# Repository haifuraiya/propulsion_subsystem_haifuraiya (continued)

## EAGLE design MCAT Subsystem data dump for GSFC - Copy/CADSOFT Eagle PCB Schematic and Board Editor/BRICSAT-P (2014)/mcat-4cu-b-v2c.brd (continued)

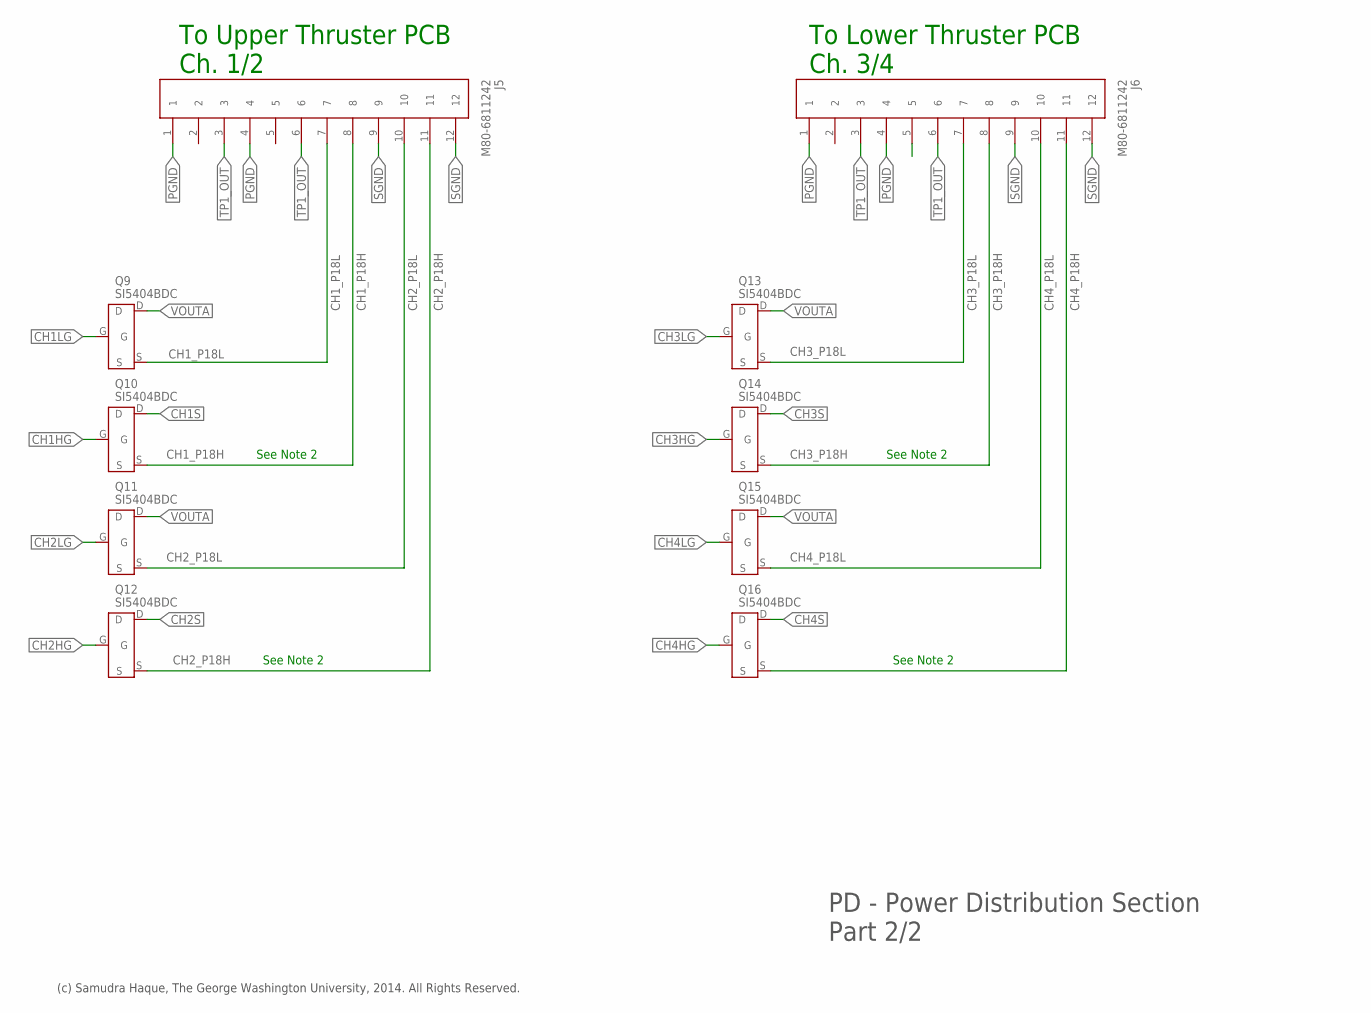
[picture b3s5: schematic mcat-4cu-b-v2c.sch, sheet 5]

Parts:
J5, J6: M80-6811242; M80-68112
Q9, Q10, Q11, Q12, Q13, Q14, Q15, Q16: SI5404BDC; 1206-8-CHIPFET

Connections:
CH1HG: Q10.G; also elsewhere on the board
CH1LG: Q9.G; also elsewhere on the board
CH1S: Q10.D; also elsewhere on the board
CH1_P18H: J5.8, Q10.S
CH1_P18L: J5.7, Q9.S
CH2HG: Q12.G; also elsewhere on the board
CH2LG: Q11.G; also elsewhere on the board
CH2S: Q12.D; also elsewhere on the board
CH2_P18H: J5.11, Q12.S
CH2_P18L: J5.10, Q11.S
CH3HG: Q14.G; also elsewhere on the board
CH3LG: Q13.G; also elsewhere on the board
CH3S: Q14.D; also elsewhere on the board
CH3_P18H: J6.8, Q14.S
CH3_P18L: J6.7, Q13.S
CH4HG: Q16.G; also elsewhere on the board
CH4LG: Q15.G; also elsewhere on the board
CH4S: Q16.D; also elsewhere on the board
CH4_P18H: J6.11, Q16.S
CH4_P18L: J6.10, Q15.S
PGND: J5.1, J5.4, J6.1, J6.4; also elsewhere on the board
SGND: J5.9, J5.12, J6.9, J6.12; also elsewhere on the board
TP1_OUT: J5.3, J5.6, J6.3, J6.6; also elsewhere on the board
VOUTA: Q9.D, Q11.D, Q13.D, Q15.D; also elsewhere on the board

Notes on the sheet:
PD - Power Distribution Section Part 2/2
(c) Samudra Haque, The George Washington University, 2014. All Rights Reserved.
See Note 2
To Upper Thruster PCB Ch. 1/2
To Lower Thruster PCB Ch. 3/4

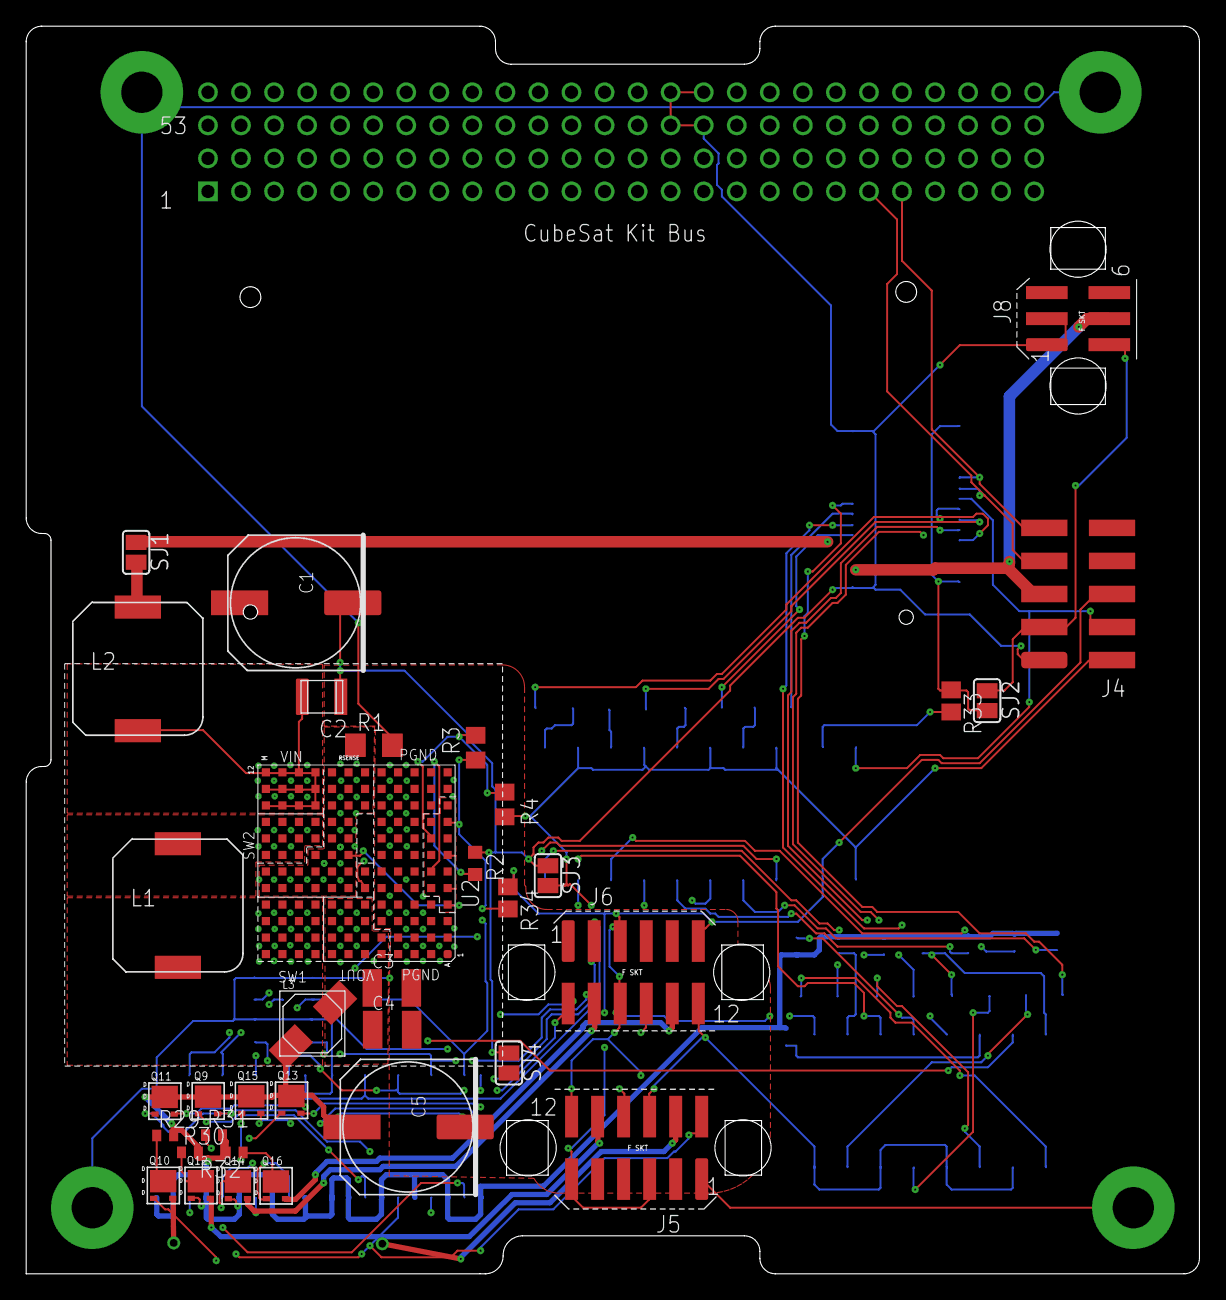
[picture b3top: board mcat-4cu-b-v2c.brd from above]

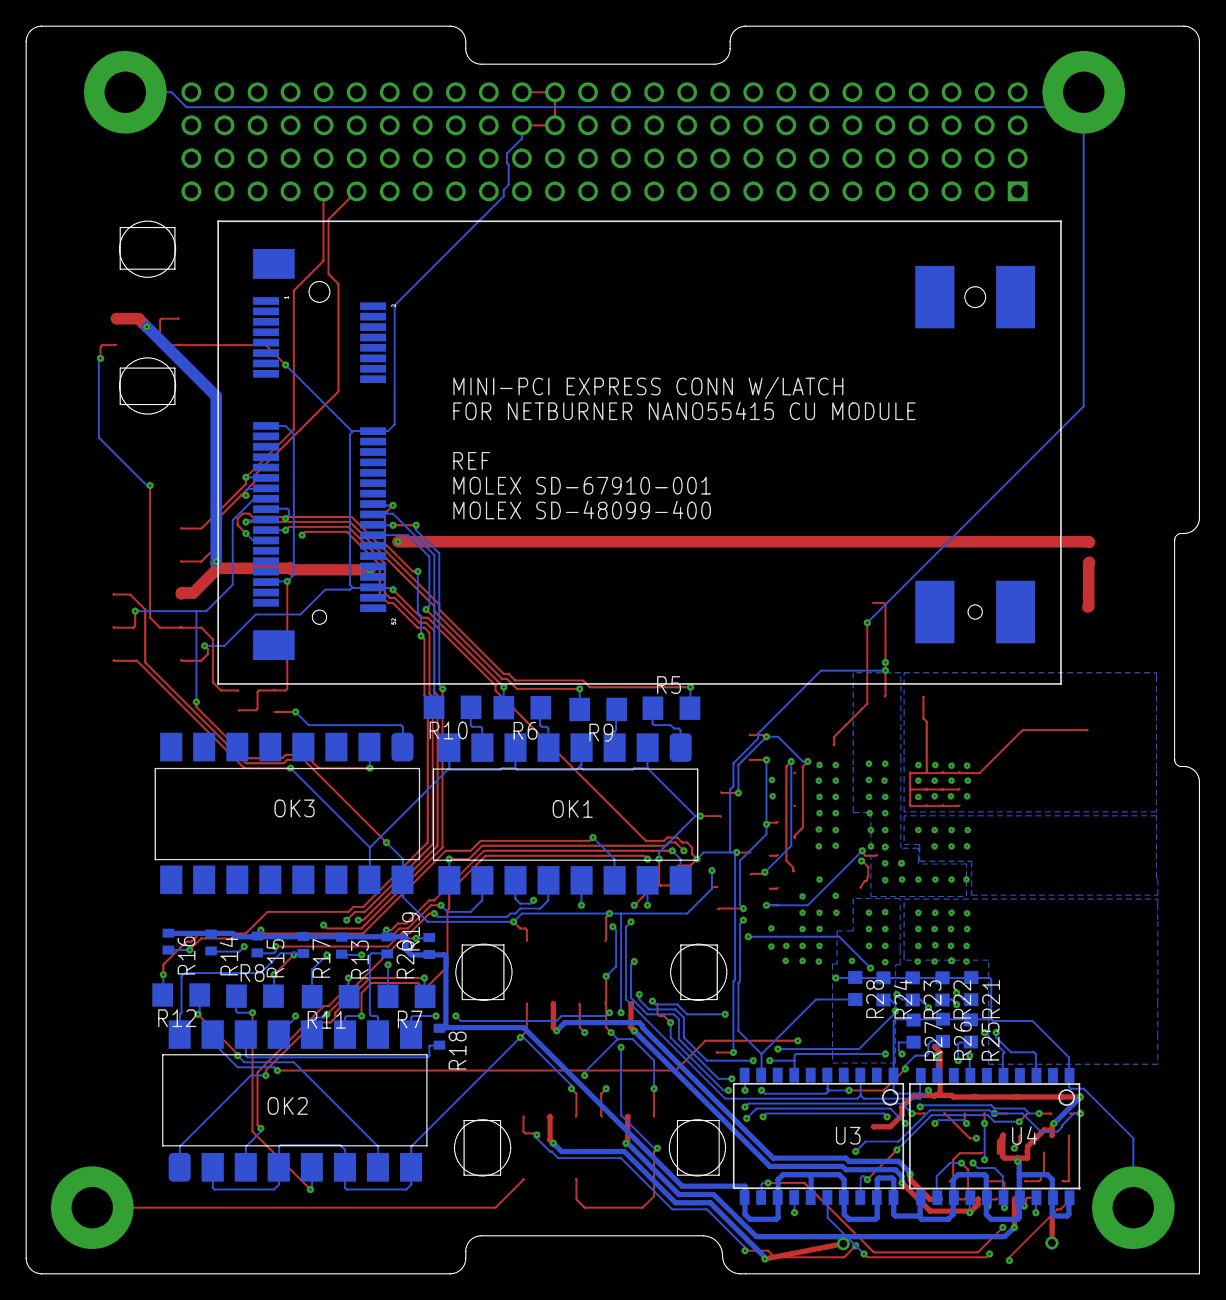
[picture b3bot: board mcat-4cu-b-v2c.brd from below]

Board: 4 copper layers, 90.2 x 95.9 mm, 70 parts (30 on the bottom side), 73 nets.

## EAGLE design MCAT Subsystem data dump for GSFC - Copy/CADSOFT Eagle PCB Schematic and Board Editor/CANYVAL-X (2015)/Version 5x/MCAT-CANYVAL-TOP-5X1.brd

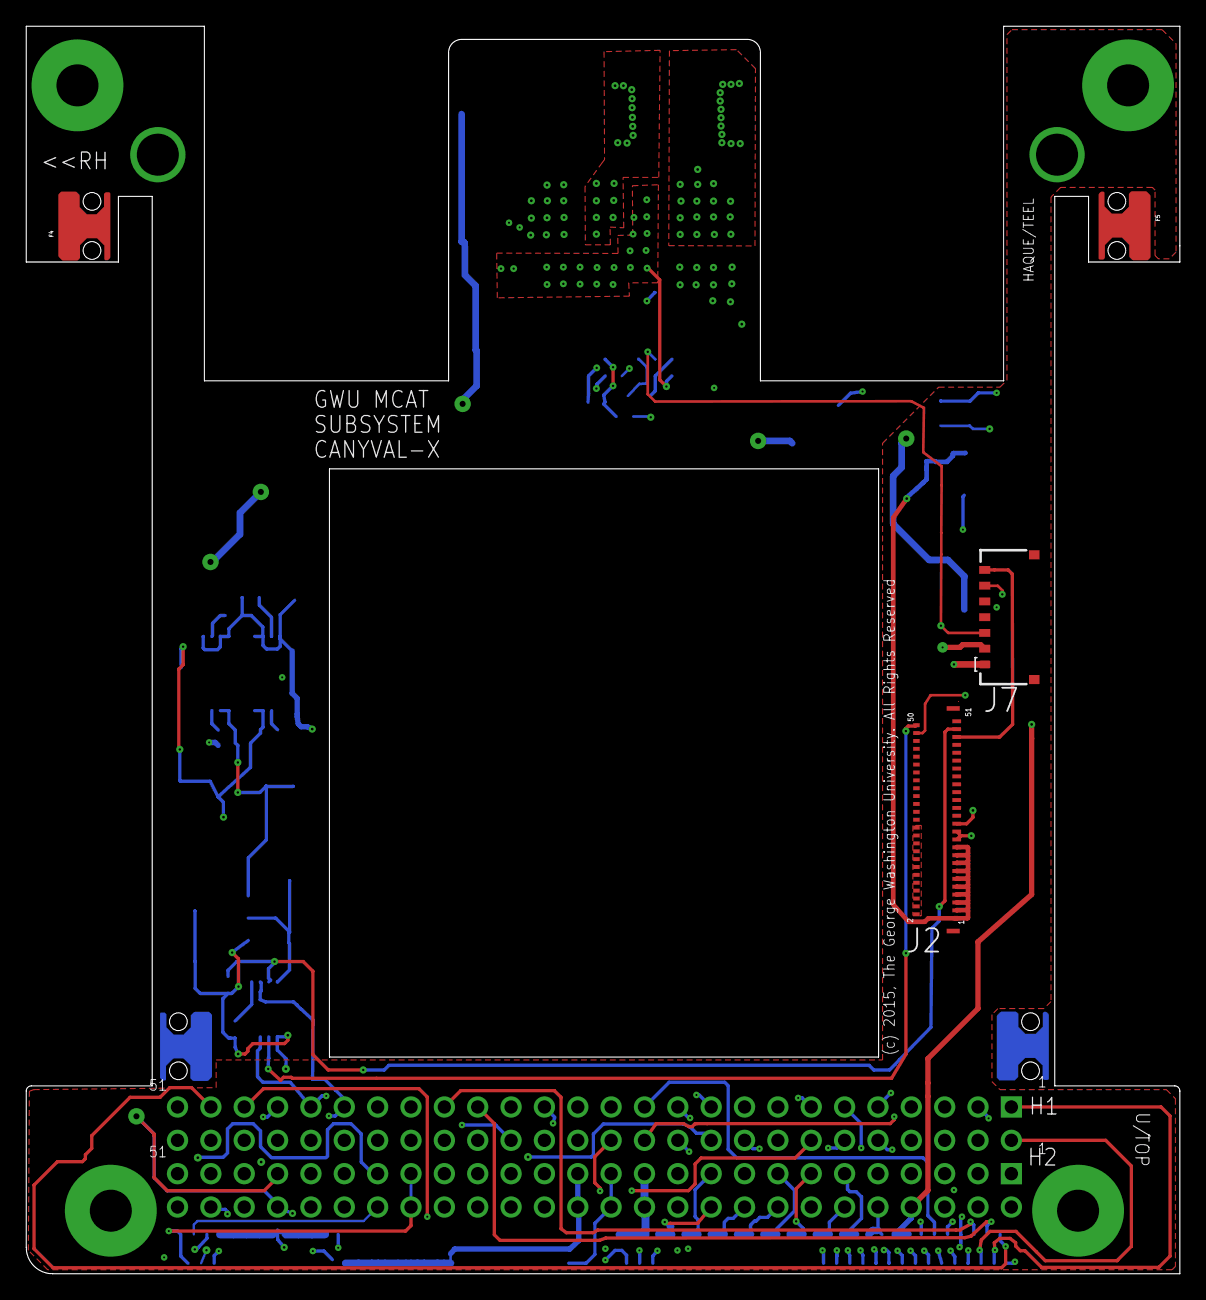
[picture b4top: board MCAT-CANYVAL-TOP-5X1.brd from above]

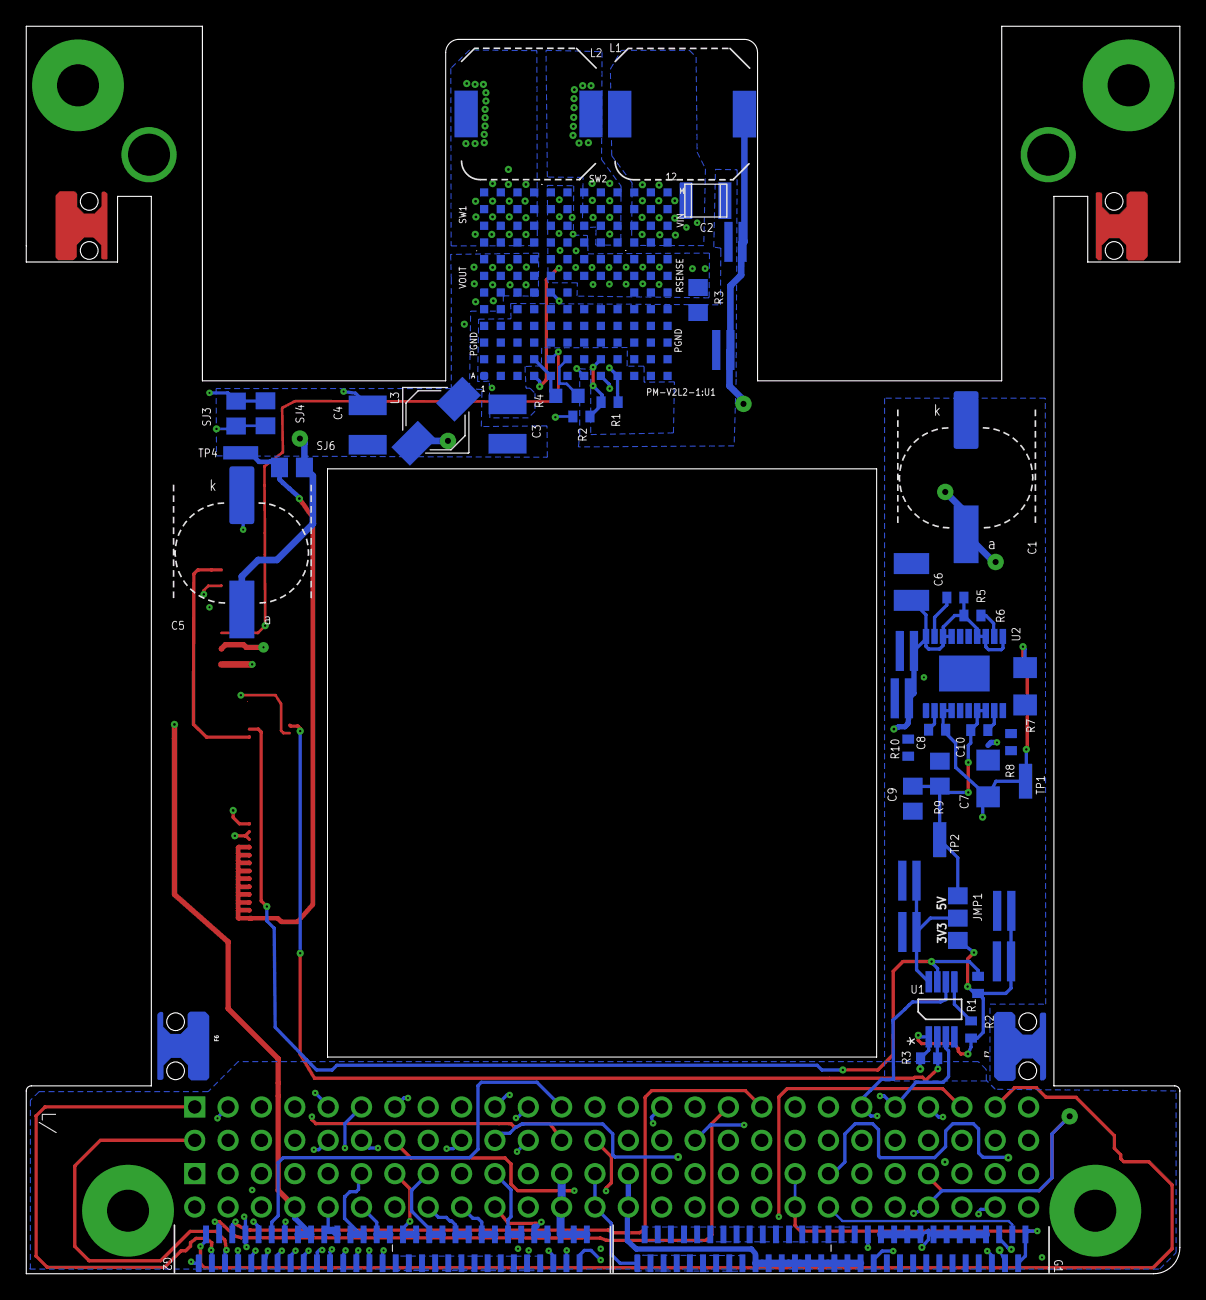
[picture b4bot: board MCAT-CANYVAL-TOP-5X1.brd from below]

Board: 6 copper layers, 87.9 x 95.0 mm, 55 parts (48 on the bottom side), 72 nets.

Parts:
B8: MCAT-4CU-C-PCB/TOP; MCAT-4CU-C-TOP-V4-BLANK
CT-V2L1-1:BC3, CT-V2L1-1:BC5: BYPASS-CAP-1UF; 0612-REV
CT-V2L1-1:BC4, CT-V2L1-1:BC6: BYPASS-CAP-0.1UF; 0612-REV
CT-V2L1-1:J7: MOLEX-78171-5007
CT-V2L1-1:JMP1: 0R-JUMPA; A0R-JMP
CT-V2L1-1:R1, CT-V2L1-1:R2, CT-V2L1-1:R3: 10k; R0402
CT-V2L1-1:U1: PCA9512ADP; SOT505-1
F4, F5, F6, F7: SMTRAM2-6-5; SMTRA-M2-6-5
GBUS-TOP1:G1, GBUS-TOP1:G2: HIROSE-FH40-60S-0.5SV
GBUS-TOP1:H1: H1-H5-INBOARD-CSK-BUS-CONN; CONN-2X26X0.1-HDR
GBUS-TOP1:H2: H2-H6-OUTBOARD-CSK-BUS-CONN; CONN-2X26X0.1-HDR
J2: MOLEX-502598-5193
PM-V2L2-1:BC1, PM-V2L2-1:BC3: BYPASS-CAP-0.1UF; 0612-REV
PM-V2L2-1:BC2, PM-V2L2-1:BC4: BYPASS-CAP-1UF; 0612-REV
PM-V2L2-1:C1, PM-V2L2-1:C5: 68uF; OS-CON-SVPF-F12
PM-V2L2-1:C2: 4.7uF; MLCC-X7R-1210
PM-V2L2-1:C3, PM-V2L2-1:C4: 10uF; C1210K
PM-V2L2-1:C6: 10u; C1210
PM-V2L2-1:C7: 10u; C1206
PM-V2L2-1:C8, PM-V2L2-1:C10: 10n; C0402
PM-V2L2-1:C9: 3.3u; C0805
PM-V2L2-1:L1: 33uH; MSS1048
PM-V2L2-1:L2: 68uH; MSS1048
PM-V2L2-1:L3: 10uH; SERIES-POWER-INDUCTORS
PM-V2L2-1:R1: 2K; R0402
PM-V2L2-1:R2: 1K; R0402
PM-V2L2-1:R3: 27mOhms; R0805
PM-V2L2-1:R4: 4k70.1%; R0603
PM-V2L2-1:R5, PM-V2L2-1:R6: 1M; R0402
PM-V2L2-1:R7: 357K; R1206
PM-V2L2-1:R8: 210K; R0402
PM-V2L2-1:R9: 619K; R0805
PM-V2L2-1:R10: 200K; R0402
PM-V2L2-1:SJ3, PM-V2L2-1:SJ4, PM-V2L2-1:SJ6: 0R; R0805
PM-V2L2-1:TP1, PM-V2L2-1:TP2, PM-V2L2-1:TP4: PCB-MINI-SMD-TESTPOINT/SQ; PCB-MINI-SMD-TESTPOINT
PM-V2L2-1:U1: LTM4609MPV#PBF; LGA-141-LTC-05-08-1840-B
PM-V2L2-1:U2: LT3030MPFE#PBF; TSSOP20-FE-CB

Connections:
CT-V2L1-1:I2C_VCC: CT-V2L1-1:BC5.1, CT-V2L1-1:BC6.1, CT-V2L1-1:JMP1.2, CT-V2L1-1:U1.8
CT-V2L1-1:N$2: CT-V2L1-1:R2.1, CT-V2L1-1:U1.5
GBUS-TOP1:G-H1-1: GBUS-TOP1:G2.2, GBUS-TOP1:H1.1
GBUS-TOP1:G-H1-2: GBUS-TOP1:G2.3, GBUS-TOP1:H1.2
GBUS-TOP1:G-H1-3: GBUS-TOP1:G2.4, GBUS-TOP1:H1.3
GBUS-TOP1:G-H1-9: GBUS-TOP1:G2.5, GBUS-TOP1:H1.9
GBUS-TOP1:G-H1-10: GBUS-TOP1:G2.6, GBUS-TOP1:H1.10
GBUS-TOP1:G-H1-11: GBUS-TOP1:G2.7, GBUS-TOP1:H1.11
GBUS-TOP1:G-H1-12: GBUS-TOP1:G2.8, GBUS-TOP1:H1.12
GBUS-TOP1:G-H1-13: GBUS-TOP1:G2.9, GBUS-TOP1:H1.13
GBUS-TOP1:G-H1-14: GBUS-TOP1:G2.10, GBUS-TOP1:H1.14
GBUS-TOP1:G-H1-18: GBUS-TOP1:G2.28, GBUS-TOP1:H1.18
GBUS-TOP1:G-H1-19: GBUS-TOP1:G1.28, GBUS-TOP1:H1.19
GBUS-TOP1:G-H1-20: GBUS-TOP1:G1.29, GBUS-TOP1:H1.20
GBUS-TOP1:G-H1-21: GBUS-TOP1:G2.34, GBUS-TOP1:H1.21
GBUS-TOP1:G-H1-22: GBUS-TOP1:G2.35, GBUS-TOP1:H1.22
GBUS-TOP1:G-H1-23: GBUS-TOP1:G2.36, GBUS-TOP1:H1.23
GBUS-TOP1:G-H1-24: GBUS-TOP1:G2.11, GBUS-TOP1:H1.24
GBUS-TOP1:G-H1-26: GBUS-TOP1:G2.29, GBUS-TOP1:H1.26
GBUS-TOP1:G-H1-29: GBUS-TOP1:G2.30, GBUS-TOP1:H1.29
GBUS-TOP1:G-H1-33: GBUS-TOP1:G2.32, GBUS-TOP1:H1.33
GBUS-TOP1:G-H1-35: GBUS-TOP1:G2.33, GBUS-TOP1:H1.35
GBUS-TOP1:G-H1-45: GBUS-TOP1:G2.14, GBUS-TOP1:H1.45
GBUS-TOP1:G-H1-47: GBUS-TOP1:G2.15, GBUS-TOP1:H1.47
GBUS-TOP1:G-H1-49: GBUS-TOP1:G2.31, GBUS-TOP1:H1.49
GBUS-TOP1:G-H2-50: GBUS-TOP1:G2.1, GBUS-TOP1:H2.50
GBUS-TOP1:M-3V3-BUS: GBUS-TOP1:G1.10, GBUS-TOP1:G1.11, GBUS-TOP1:G1.12, GBUS-TOP1:G1.13, GBUS-TOP1:G1.14, GBUS-TOP1:G1.15, GBUS-TOP1:G1.16, GBUS-TOP1:G1.17, GBUS-TOP1:G1.18, GBUS-TOP1:H2.27, GBUS-TOP1:H2.28
GBUS-TOP1:M-5V-BUS: GBUS-TOP1:G1.1, GBUS-TOP1:G1.2, GBUS-TOP1:G1.3, GBUS-TOP1:G1.4, GBUS-TOP1:G1.5, GBUS-TOP1:G1.6, GBUS-TOP1:G1.7, GBUS-TOP1:G1.8, GBUS-TOP1:G1.9, GBUS-TOP1:H2.25, GBUS-TOP1:H2.26
GBUS-TOP1:M-5V-USB-CHG: GBUS-TOP1:G1.48, GBUS-TOP1:H1.32
GBUS-TOP1:M-12V-BUS: GBUS-TOP1:G2.58, GBUS-TOP1:G2.59, GBUS-TOP1:G2.60, GBUS-TOP1:H2.23, GBUS-TOP1:H2.24
GBUS-TOP1:M-SW2-12V: GBUS-TOP1:G2.40, GBUS-TOP1:G2.41, GBUS-TOP1:H2.10
GBUS-TOP1:M-SW3-BAT: GBUS-TOP1:G2.42, GBUS-TOP1:G2.43, GBUS-TOP1:H2.11
GBUS-TOP1:M-SW4-BAT: GBUS-TOP1:G2.44, GBUS-TOP1:G2.45, GBUS-TOP1:H2.12
GBUS-TOP1:M-SW5-5V: GBUS-TOP1:G2.46, GBUS-TOP1:G2.47, GBUS-TOP1:H2.13
GBUS-TOP1:M-SW6-5V: GBUS-TOP1:G2.48, GBUS-TOP1:G2.49, GBUS-TOP1:H2.15
GBUS-TOP1:M-SW7-5V: GBUS-TOP1:G2.50, GBUS-TOP1:G2.51, GBUS-TOP1:H2.16
GBUS-TOP1:M-SW8-3V3: GBUS-TOP1:G2.52, GBUS-TOP1:G2.53, GBUS-TOP1:H2.18
GBUS-TOP1:M-SW9-3V3: GBUS-TOP1:G2.54, GBUS-TOP1:G2.55, GBUS-TOP1:H2.19
GBUS-TOP1:M-SW10-3V3: GBUS-TOP1:G2.56, GBUS-TOP1:G2.57, GBUS-TOP1:H2.20
GBUS-TOP1:RBF_SW: GBUS-TOP1:G1.30, GBUS-TOP1:G1.60, GBUS-TOP1:H2.37, GBUS-TOP1:H2.38
GBUS-TOP1:SEP_SW1: GBUS-TOP1:G1.58, GBUS-TOP1:H2.39
GBUS-TOP1:SEP_SW2: GBUS-TOP1:G1.59, GBUS-TOP1:H2.40
GND: B8.GND, B8.GND@1, B8.GND@2, B8.GND@3, B8.GND@4, B8.GND@6, CT-V2L1-1:BC3.2, CT-V2L1-1:BC4.2, CT-V2L1-1:BC5.2, CT-V2L1-1:BC6.2, CT-V2L1-1:J7.5, CT-V2L1-1:U1.4, GBUS-TOP1:G1.19, GBUS-TOP1:G1.20, GBUS-TOP1:G1.21, GBUS-TOP1:G1.22, GBUS-TOP1:G1.23, GBUS-TOP1:G1.24, GBUS-TOP1:G1.25, GBUS-TOP1:G1.26, GBUS-TOP1:G1.27, GBUS-TOP1:G1.31, GBUS-TOP1:G1.32, GBUS-TOP1:G1.33, GBUS-TOP1:G1.34, GBUS-TOP1:G1.35, GBUS-TOP1:G1.36, GBUS-TOP1:G1.37, GBUS-TOP1:G1.38, GBUS-TOP1:G1.39, GBUS-TOP1:G1.40, GBUS-TOP1:G1.41, GBUS-TOP1:G1.42, GBUS-TOP1:G1.43, GBUS-TOP1:G1.44, GBUS-TOP1:G1.45, GBUS-TOP1:G1.46, GBUS-TOP1:G1.47, GBUS-TOP1:G2.16, GBUS-TOP1:G2.17, GBUS-TOP1:G2.18, GBUS-TOP1:G2.19, GBUS-TOP1:G2.20, GBUS-TOP1:G2.21, GBUS-TOP1:G2.22, GBUS-TOP1:G2.23, GBUS-TOP1:G2.24, GBUS-TOP1:G2.25, GBUS-TOP1:G2.26, GBUS-TOP1:G2.27, GBUS-TOP1:G2.37, GBUS-TOP1:H2.9, GBUS-TOP1:H2.14, GBUS-TOP1:H2.17, GBUS-TOP1:H2.21, GBUS-TOP1:H2.22, GBUS-TOP1:H2.29, GBUS-TOP1:H2.30, GBUS-TOP1:H2.32, GBUS-TOP1:H2.47, GBUS-TOP1:H2.48, J2.2, J2.4, J2.6, J2.8, J2.10, J2.12, J2.14, J2.16, J2.18, J2.20, J2.22, J2.24, PM-V2L2-1:BC1.2, PM-V2L2-1:BC2.2, PM-V2L2-1:BC3.2, PM-V2L2-1:BC4.2, PM-V2L2-1:C1.K1, PM-V2L2-1:C2.2, PM-V2L2-1:C3.2, PM-V2L2-1:C4.2, PM-V2L2-1:C5.K1, PM-V2L2-1:C6.2, PM-V2L2-1:C7.2, PM-V2L2-1:C9.2, PM-V2L2-1:R3.2, PM-V2L2-1:R4.1, PM-V2L2-1:R8.1, PM-V2L2-1:R10.1, PM-V2L2-1:SJ3.1, PM-V2L2-1:SJ4.1, PM-V2L2-1:U1.A1, PM-V2L2-1:U1.A2, PM-V2L2-1:U1.A3, PM-V2L2-1:U1.A5, PM-V2L2-1:U1.A11, PM-V2L2-1:U1.A12, PM-V2L2-1:U1.B1, PM-V2L2-1:U1.B2, PM-V2L2-1:U1.B3, PM-V2L2-1:U1.B4, PM-V2L2-1:U1.B10, PM-V2L2-1:U1.B11, PM-V2L2-1:U1.B12, PM-V2L2-1:U1.C1, PM-V2L2-1:U1.C2, PM-V2L2-1:U1.C3, PM-V2L2-1:U1.C4, PM-V2L2-1:U1.C5, PM-V2L2-1:U1.C6, PM-V2L2-1:U1.C7, PM-V2L2-1:U1.C8, PM-V2L2-1:U1.C9, PM-V2L2-1:U1.C10, PM-V2L2-1:U1.C11, PM-V2L2-1:U1.C12, PM-V2L2-1:U1.D1, PM-V2L2-1:U1.D2, PM-V2L2-1:U1.D3, PM-V2L2-1:U1.D4, PM-V2L2-1:U1.D5, PM-V2L2-1:U1.D6, PM-V2L2-1:U1.D7, PM-V2L2-1:U1.D8, PM-V2L2-1:U1.D9, PM-V2L2-1:U1.D10, PM-V2L2-1:U1.D11, PM-V2L2-1:U1.D12, PM-V2L2-1:U1.E3, PM-V2L2-1:U1.E4, PM-V2L2-1:U1.E5, PM-V2L2-1:U1.E6, PM-V2L2-1:U1.E7, PM-V2L2-1:U1.E8, PM-V2L2-1:U1.E9, PM-V2L2-1:U1.E10, PM-V2L2-1:U1.E11, PM-V2L2-1:U1.E12, PM-V2L2-1:U2.5, PM-V2L2-1:U2.6, PM-V2L2-1:U2.15, PM-V2L2-1:U2.16, PM-V2L2-1:U2.21
MCAT_SCL: CT-V2L1-1:R3.1, CT-V2L1-1:U1.2, J2.50
MCAT_SDA: CT-V2L1-1:R1.1, CT-V2L1-1:U1.7, J2.49
P3: CT-V2L1-1:BC3.1, CT-V2L1-1:BC4.1, CT-V2L1-1:JMP1.1, CT-V2L1-1:R1.2, CT-V2L1-1:R2.2, CT-V2L1-1:R3.2, CT-V2L1-1:U1.1, J2.21, J2.23, PM-V2L2-1:C7.1, PM-V2L2-1:C8.1, PM-V2L2-1:R7.2, PM-V2L2-1:TP1.1, PM-V2L2-1:U2.3, PM-V2L2-1:U2.4
P5: CT-V2L1-1:JMP1.3, PM-V2L2-1:C9.1, PM-V2L2-1:C10.1, PM-V2L2-1:R9.2, PM-V2L2-1:TP2.1, PM-V2L2-1:U2.7, PM-V2L2-1:U2.8
P12_IN: CT-V2L1-1:J7.2, GBUS-TOP1:G2.38, GBUS-TOP1:G2.39, GBUS-TOP1:H2.8, PM-V2L2-1:BC1.1, PM-V2L2-1:BC2.1, PM-V2L2-1:C6.1, PM-V2L2-1:R5.2, PM-V2L2-1:R6.2, PM-V2L2-1:U2.11, PM-V2L2-1:U2.13, PM-V2L2-1:U2.14, PM-V2L2-1:U2.17, PM-V2L2-1:U2.18, PM-V2L2-1:U2.20
PGOOD_PMA: CT-V2L1-1:J7.3, PM-V2L2-1:U1.B5
PM-V2L2-1:ADJ1: PM-V2L2-1:R7.1, PM-V2L2-1:R8.2, PM-V2L2-1:U2.1
PM-V2L2-1:ADJ2: PM-V2L2-1:R9.1, PM-V2L2-1:R10.2, PM-V2L2-1:U2.10
PM-V2L2-1:BYP1: PM-V2L2-1:C8.2, PM-V2L2-1:U2.2
PM-V2L2-1:BYP2: PM-V2L2-1:C10.2, PM-V2L2-1:U2.9
PM-V2L2-1:INTVCC: PM-V2L2-1:R1.1, PM-V2L2-1:U1.A9, PM-V2L2-1:U1.F5
PM-V2L2-1:P18_OUT: PM-V2L2-1:C5.A1, PM-V2L2-1:L3.2, PM-V2L2-1:SJ6.1
PM-V2L2-1:PWRDGD2: PM-V2L2-1:R6.1, PM-V2L2-1:U2.12
PM-V2L2-1:PWRGD1: PM-V2L2-1:R5.1, PM-V2L2-1:U2.19
PM-V2L2-1:RSENSE: PM-V2L2-1:R3.1, PM-V2L2-1:U1.A4, PM-V2L2-1:U1.F10, PM-V2L2-1:U1.F11, PM-V2L2-1:U1.F12, PM-V2L2-1:U1.G5, PM-V2L2-1:U1.G6, PM-V2L2-1:U1.G7, PM-V2L2-1:U1.G8, PM-V2L2-1:U1.G9, PM-V2L2-1:U1.G10, PM-V2L2-1:U1.G11, PM-V2L2-1:U1.G12, PM-V2L2-1:U1.H5, PM-V2L2-1:U1.H6, PM-V2L2-1:U1.H7, PM-V2L2-1:U1.H8, PM-V2L2-1:U1.H9, PM-V2L2-1:U1.H10, PM-V2L2-1:U1.H11, PM-V2L2-1:U1.H12, PM-V2L2-1:U1.J5, PM-V2L2-1:U1.J6, PM-V2L2-1:U1.J7, PM-V2L2-1:U1.K5, PM-V2L2-1:U1.K6, PM-V2L2-1:U1.L5, PM-V2L2-1:U1.L6, PM-V2L2-1:U1.M5, PM-V2L2-1:U1.M6
PM-V2L2-1:SETFREQ: PM-V2L2-1:R1.2, PM-V2L2-1:R2.1, PM-V2L2-1:U1.B8
PM-V2L2-1:SGND: PM-V2L2-1:R2.2, PM-V2L2-1:SJ3.2, PM-V2L2-1:SJ4.2, PM-V2L2-1:U1.A7
PM-V2L2-1:SW1: PM-V2L2-1:L2.2, PM-V2L2-1:U1.SW1@J1, PM-V2L2-1:U1.SW1@J2, PM-V2L2-1:U1.SW1@J3, PM-V2L2-1:U1.SW1@J4, PM-V2L2-1:U1.SW1@K1, PM-V2L2-1:U1.SW1@K2, PM-V2L2-1:U1.SW1@K3, PM-V2L2-1:U1.SW1@K4, PM-V2L2-1:U1.SW1@L1, PM-V2L2-1:U1.SW1@L2, PM-V2L2-1:U1.SW1@L3, PM-V2L2-1:U1.SW1@L4, PM-V2L2-1:U1.SW1@M1, PM-V2L2-1:U1.SW1@M2, PM-V2L2-1:U1.SW1@M3, PM-V2L2-1:U1.SW1@M4
PM-V2L2-1:SW2: PM-V2L2-1:L2.1, PM-V2L2-1:U1.J8, PM-V2L2-1:U1.J9, PM-V2L2-1:U1.K7, PM-V2L2-1:U1.K8, PM-V2L2-1:U1.K9, PM-V2L2-1:U1.L7, PM-V2L2-1:U1.L8, PM-V2L2-1:U1.L9, PM-V2L2-1:U1.M7, PM-V2L2-1:U1.M8, PM-V2L2-1:U1.M9
PM-V2L2-1:VFB: PM-V2L2-1:R4.2, PM-V2L2-1:U1.B6
PM-V2L2-1:VIN: PM-V2L2-1:C2.1, PM-V2L2-1:L1.2, PM-V2L2-1:U1.J10, PM-V2L2-1:U1.J11, PM-V2L2-1:U1.J12, PM-V2L2-1:U1.K10, PM-V2L2-1:U1.K11, PM-V2L2-1:U1.K12, PM-V2L2-1:U1.L10, PM-V2L2-1:U1.L11, PM-V2L2-1:U1.L12, PM-V2L2-1:U1.M10, PM-V2L2-1:U1.M11, PM-V2L2-1:U1.M12
PM-V2L2-1:VOUT: PM-V2L2-1:C3.1, PM-V2L2-1:C4.1, PM-V2L2-1:L3.1, PM-V2L2-1:U1.E1, PM-V2L2-1:U1.E2, PM-V2L2-1:U1.F1, PM-V2L2-1:U1.F2, PM-V2L2-1:U1.F3, PM-V2L2-1:U1.F4, PM-V2L2-1:U1.G1, PM-V2L2-1:U1.G2, PM-V2L2-1:U1.G3, PM-V2L2-1:U1.G4, PM-V2L2-1:U1.H2, PM-V2L2-1:U1.H3, PM-V2L2-1:U1.H4, PM-V2L2-1:U1.VOUT
SCLIN: CT-V2L1-1:U1.3, GBUS-TOP1:G2.13, GBUS-TOP1:H1.43
SDAIN: CT-V2L1-1:U1.6, GBUS-TOP1:G2.12, GBUS-TOP1:H1.41
SW_RUNPMA: J2.25, PM-V2L2-1:U1.A8
UART0_RX: CT-V2L1-1:J7.6, J2.48
UART0_TX: CT-V2L1-1:J7.7, J2.47
VBATT_IN: CT-V2L1-1:J7.1, GBUS-TOP1:G1.49, GBUS-TOP1:G1.50, GBUS-TOP1:G1.51, GBUS-TOP1:G1.52, GBUS-TOP1:G1.53, GBUS-TOP1:G1.54, GBUS-TOP1:G1.55, GBUS-TOP1:G1.56, GBUS-TOP1:G1.57, GBUS-TOP1:H2.45, GBUS-TOP1:H2.46, PM-V2L2-1:BC3.1, PM-V2L2-1:BC4.1, PM-V2L2-1:C1.A1, PM-V2L2-1:L1.1
VOUTA: J2.1, J2.3, J2.5, J2.7, J2.9, J2.11, J2.13, J2.15, J2.17, J2.19, PM-V2L2-1:SJ6.2, PM-V2L2-1:TP4.1

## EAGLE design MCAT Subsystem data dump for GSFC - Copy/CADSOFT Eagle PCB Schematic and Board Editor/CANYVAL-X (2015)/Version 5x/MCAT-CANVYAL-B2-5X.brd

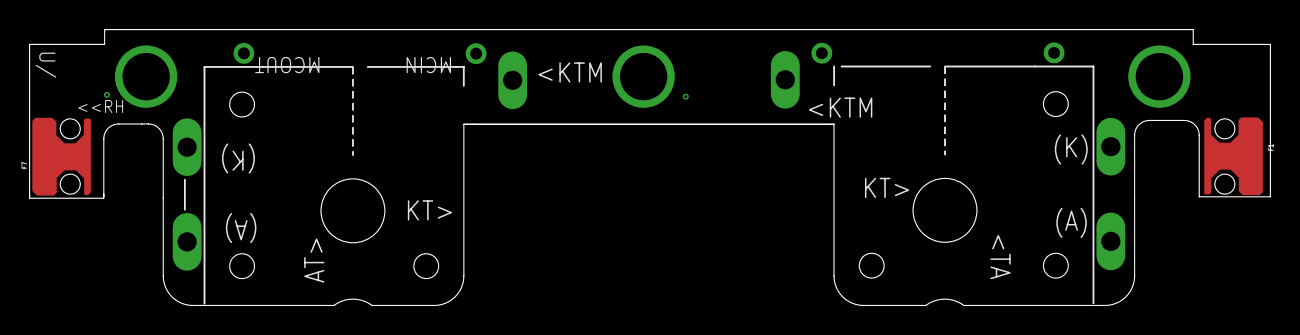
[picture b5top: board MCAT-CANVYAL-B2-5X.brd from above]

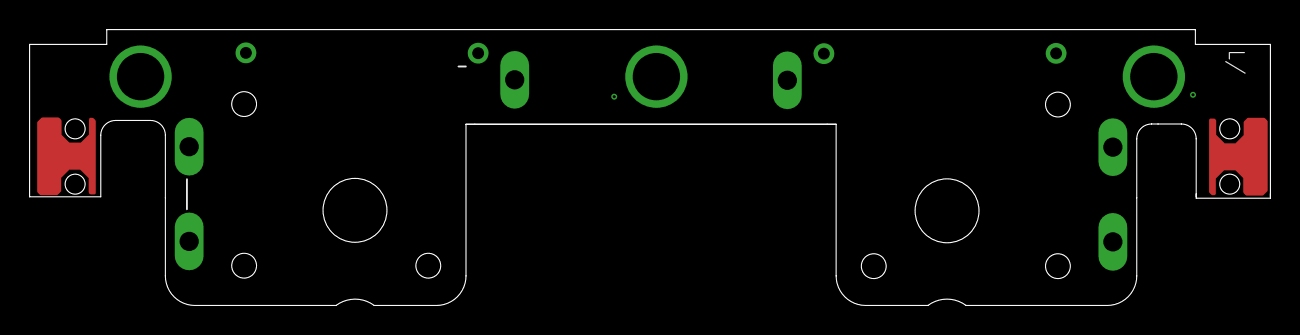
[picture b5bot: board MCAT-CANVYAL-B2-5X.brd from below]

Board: 6 copper layers, 83.9 x 18.6 mm, 5 parts (2 on the bottom side), 5 nets.

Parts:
B3: MCAT-4CU-C-PCB/MID; MCAT-4CU-C-MID-V4-BLANK
F1, F7: SMTRAM2-6-5; SMTRA-M2-6-5
THL2:TH2: MCAT-TH-G4X-YONSEI/LH; MCAT-TH-G4X-LH
THR1:TH2: MCAT-TH-G4X-YONSEI/RH; MCAT-TH-G4X-RH

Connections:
GND: B3.GND, B3.GND@2, B3.GND@3
unnamed: THR1:TH2.K, THR1:TH2.MCOUT
unnamed: THL2:TH2.K, THL2:TH2.MCOUT
THL2:KTMMCIN: THL2:TH2.KTM, THL2:TH2.MCIN
THR1:KTMMCIN: THR1:TH2.KTM, THR1:TH2.MCIN

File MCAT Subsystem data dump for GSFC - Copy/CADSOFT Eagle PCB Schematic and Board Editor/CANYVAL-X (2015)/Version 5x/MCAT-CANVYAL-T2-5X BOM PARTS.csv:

"Part";"Value";"Device";"Package";"Description";"COPYRIGHT";"MF";"MPN";"PCBLABEL";
"B4";"MCAT-4CU-C-PCB/MID";"MCAT-4CU-C-PCB/MID";"MCAT-4CU-C-MID-V4-BLANK";"";"(c) 2015, GWU";"";"";"T2";
"F6";"SMTRAM2-6-5";"SMTRAM2-6-5";"SMTRA-M2-6-5";"Type SMTRA - ReelFast Surface Mount Right Angle (R'ANGLE) Fastener (Metric)";"";"Penn Engineering";"SMTRAM2-6-5-DT";"";
"F7";"SMTRAM2-6-5";"SMTRAM2-6-5";"SMTRA-M2-6-5";"Type SMTRA - ReelFast Surface Mount Right Angle (R'ANGLE) Fastener (Metric)";"";"Penn Engineering";"SMTRAM2-6-5-DT";"";
"THL2:TH2";"MCAT-TH-G4X-YONSEI/LH";"MCAT-TH-G4X-YONSEI/LH";"MCAT-TH-G4X-LH";"Thruster for CANYVAL bus. Note LH and RH orientations are separate, and opposing pin arrangements. Layers are also flipped.";"";"";"";"";
"THR1:TH2";"MCAT-TH-G4X-YONSEI/RH";"MCAT-TH-G4X-YONSEI/RH";"MCAT-TH-G4X-RH";"Thruster for CANYVAL bus. Note LH and RH orientations are separate, and opposing pin arrangements. Layers are also flipped.";"";"";"";"";

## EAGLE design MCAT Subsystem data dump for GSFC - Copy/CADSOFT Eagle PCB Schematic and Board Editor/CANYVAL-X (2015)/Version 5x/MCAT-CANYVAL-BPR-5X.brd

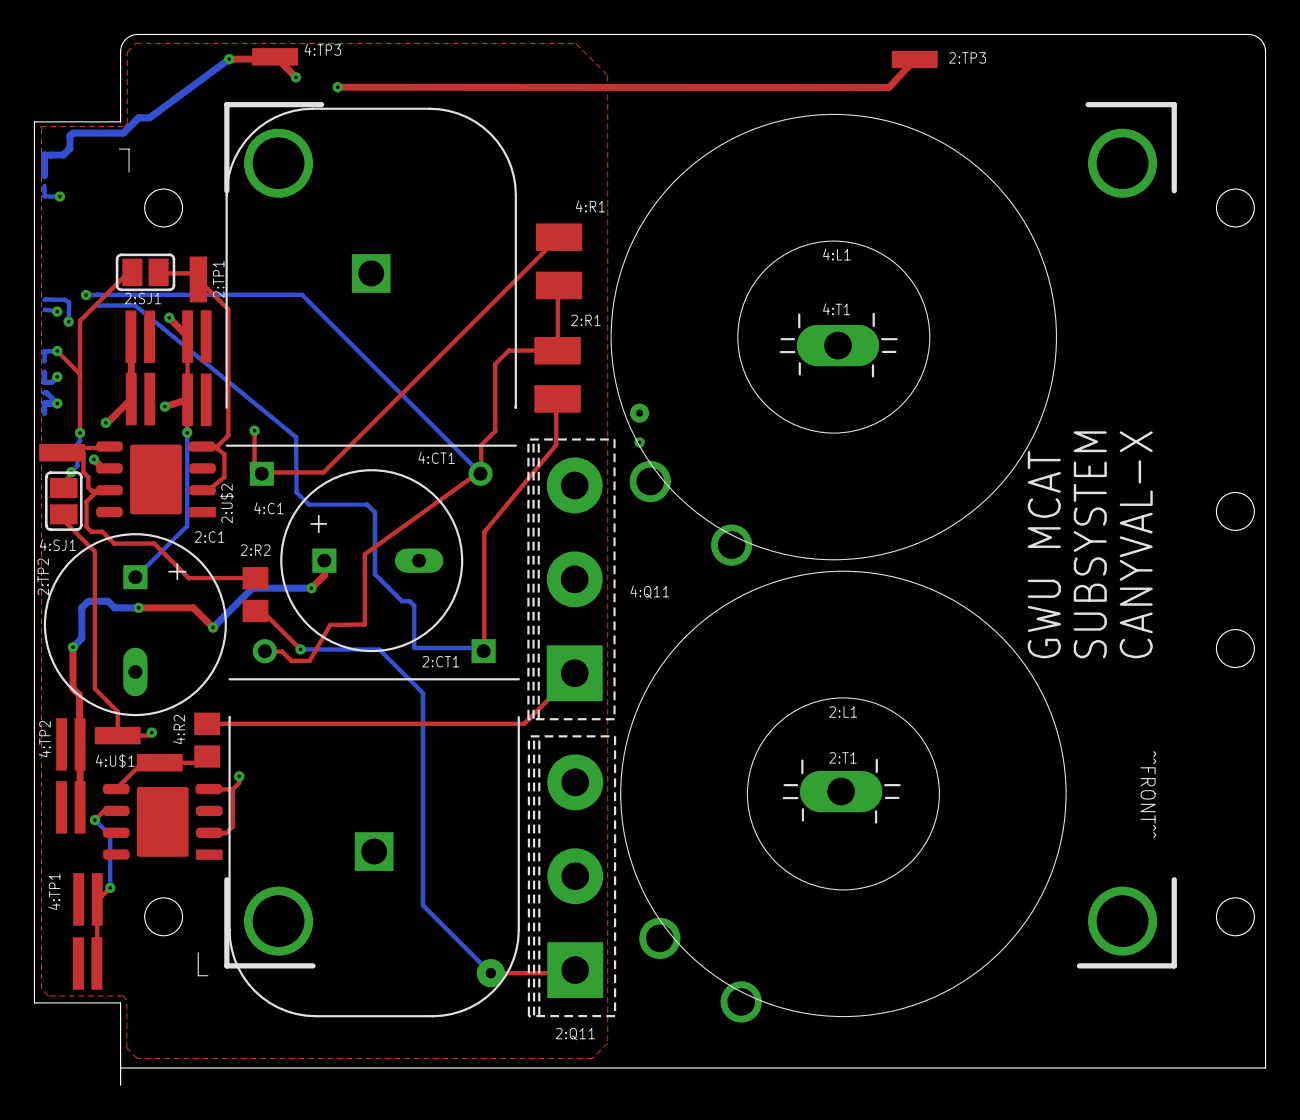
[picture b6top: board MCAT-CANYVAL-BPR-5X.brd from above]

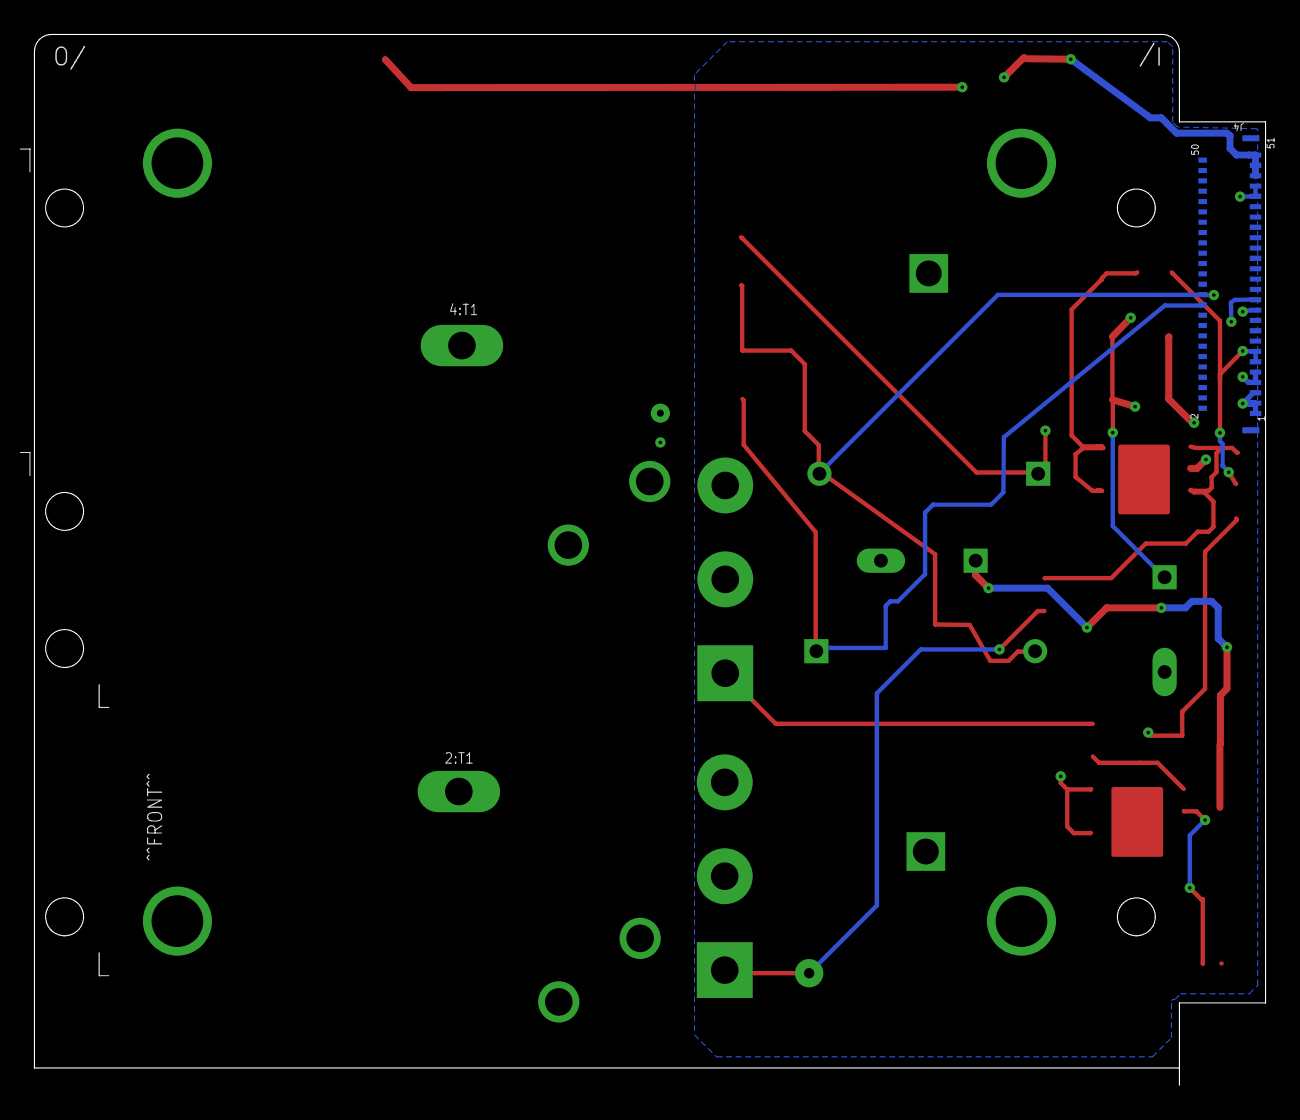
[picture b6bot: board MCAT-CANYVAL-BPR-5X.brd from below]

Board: 6 copper layers, 71.5 x 61.0 mm, 40 parts (5 on the bottom side), 17 nets.

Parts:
B1: MCAT-4CU-C-PCB/BPR; MCAT-4CU-C-BPR-V4-BLANK
F1, F2, F3, F4, F5, F7: SMTRAM2-6-5-RA; SMTRA-M2-6-5-RA
J4: MOLEX-502598-5193
PPU-V8C1-2:BC1, PPU-V8C1-2:BC3, PPU-V8C1-4:BC1, PPU-V8C1-4:BC3: BYPASS-CAP-0.1UF; 0612-REV
PPU-V8C1-2:BC2, PPU-V8C1-2:BC4, PPU-V8C1-4:BC2, PPU-V8C1-4:BC4: BYPASS-CAP-1UF; 0612-REV
PPU-V8C1-2:C1, PPU-V8C1-4:C1: 680uF/20WV; CHEMI-CON-PSG-JB5
PPU-V8C1-2:CT1, PPU-V8C1-4:CT1: MURATA-5600-CURR-XFR/RA; MURATA-5600-SERIES-CURR-XFR-RA
PPU-V8C1-2:L1, PPU-V8C1-4:L1: PPUV8-INDUCTOR-V2
PPU-V8C1-2:Q11, PPU-V8C1-4:Q11: IXYH30N120C3D1; IXYS-TO-247-AD-VERT
PPU-V8C1-2:R1, PPU-V8C1-4:R1: 15R; R1210
PPU-V8C1-2:R2, PPU-V8C1-4:R2: 1K; R0805
PPU-V8C1-2:SJ1, PPU-V8C1-4:SJ1: 0R; SJ
PPU-V8C1-2:T1, PPU-V8C1-4:T1: MCAT-SPADE-TERMINAL; SPADE-TERMINAL-FLANGED-NYLON-INSULATED
PPU-V8C1-2:TP1, PPU-V8C1-2:TP2, PPU-V8C1-2:TP3, PPU-V8C1-4:TP1, PPU-V8C1-4:TP2, PPU-V8C1-4:TP3: PCB-MINI-SMD-TESTPOINT/SQ; PCB-MINI-SMD-TESTPOINT
PPU-V8C1-2:U$1, PPU-V8C1-4:U$1: IXDN604/SI; IXYS-SI-8PIN-POWER-SOIC

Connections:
AGND_ADC_GROUND: J4.21, J4.24, PPU-V8C1-2:CT1.3, PPU-V8C1-2:R1.2, PPU-V8C1-4:CT1.3, PPU-V8C1-4:R1.2
CH2_P18H: J4.1, J4.3, J4.5, PPU-V8C1-2:BC1.1, PPU-V8C1-2:BC2.1, PPU-V8C1-2:C1.POS, PPU-V8C1-2:L1.1, PPU-V8C1-2:TP3.1
CH2_P18L: J4.7, J4.9, PPU-V8C1-2:BC3.1, PPU-V8C1-2:BC4.1, PPU-V8C1-2:U$1.6
CH2_SENSE+: J4.22, PPU-V8C1-2:CT1.1, PPU-V8C1-2:R1.1
CH4_P18H: J4.47, J4.49, J4.51, PPU-V8C1-4:BC1.1, PPU-V8C1-4:BC2.1, PPU-V8C1-4:C1.POS, PPU-V8C1-4:L1.1, PPU-V8C1-4:TP3.1
CH4_P18L: J4.43, J4.45, PPU-V8C1-4:BC3.1, PPU-V8C1-4:BC4.1, PPU-V8C1-4:U$1.6
CH4_SENSE+: J4.23, PPU-V8C1-4:CT1.1, PPU-V8C1-4:R1.1
GND: J4.2, J4.4, J4.6, J4.8, J4.10, J4.12, J4.14, J4.42, J4.44, J4.46, J4.48, J4.50, PPU-V8C1-2:BC1.2, PPU-V8C1-2:BC2.2, PPU-V8C1-2:BC3.2, PPU-V8C1-2:BC4.2, PPU-V8C1-2:C1.NEG, PPU-V8C1-2:CT1.PPU-K, PPU-V8C1-2:Q11.E, PPU-V8C1-2:U$1.3, PPU-V8C1-2:U$1.9, PPU-V8C1-4:BC1.2, PPU-V8C1-4:BC2.2, PPU-V8C1-4:BC3.2, PPU-V8C1-4:BC4.2, PPU-V8C1-4:C1.NEG, PPU-V8C1-4:CT1.PPU-K, PPU-V8C1-4:Q11.E, PPU-V8C1-4:U$1.3, PPU-V8C1-4:U$1.9
PPU-V8C1-2:N$2: PPU-V8C1-2:Q11.G, PPU-V8C1-2:R2.2
PPU-V8C1-2:PPU-A: PPU-V8C1-2:L1.2, PPU-V8C1-2:Q11.C, PPU-V8C1-2:T1.T
PPU-V8C1-2:TPIPD_IN: PPU-V8C1-2:SJ1.2, PPU-V8C1-2:TP1.1, PPU-V8C1-2:U$1.2, PPU-V8C1-2:U$1.4
PPU-V8C1-2:TPIPD_OUT: PPU-V8C1-2:R2.1, PPU-V8C1-2:TP2.1, PPU-V8C1-2:U$1.5, PPU-V8C1-2:U$1.7
PPU-V8C1-4:N$2: PPU-V8C1-4:Q11.G, PPU-V8C1-4:R2.2
PPU-V8C1-4:PPU-A: PPU-V8C1-4:L1.2, PPU-V8C1-4:Q11.C, PPU-V8C1-4:T1.T
PPU-V8C1-4:TPIPD_IN: PPU-V8C1-4:SJ1.2, PPU-V8C1-4:TP1.1, PPU-V8C1-4:U$1.2, PPU-V8C1-4:U$1.4
PPU-V8C1-4:TPIPD_OUT: PPU-V8C1-4:R2.1, PPU-V8C1-4:TP2.1, PPU-V8C1-4:U$1.5, PPU-V8C1-4:U$1.7
TP1_OUT: J4.11, J4.13, PPU-V8C1-2:SJ1.1, PPU-V8C1-4:SJ1.1
